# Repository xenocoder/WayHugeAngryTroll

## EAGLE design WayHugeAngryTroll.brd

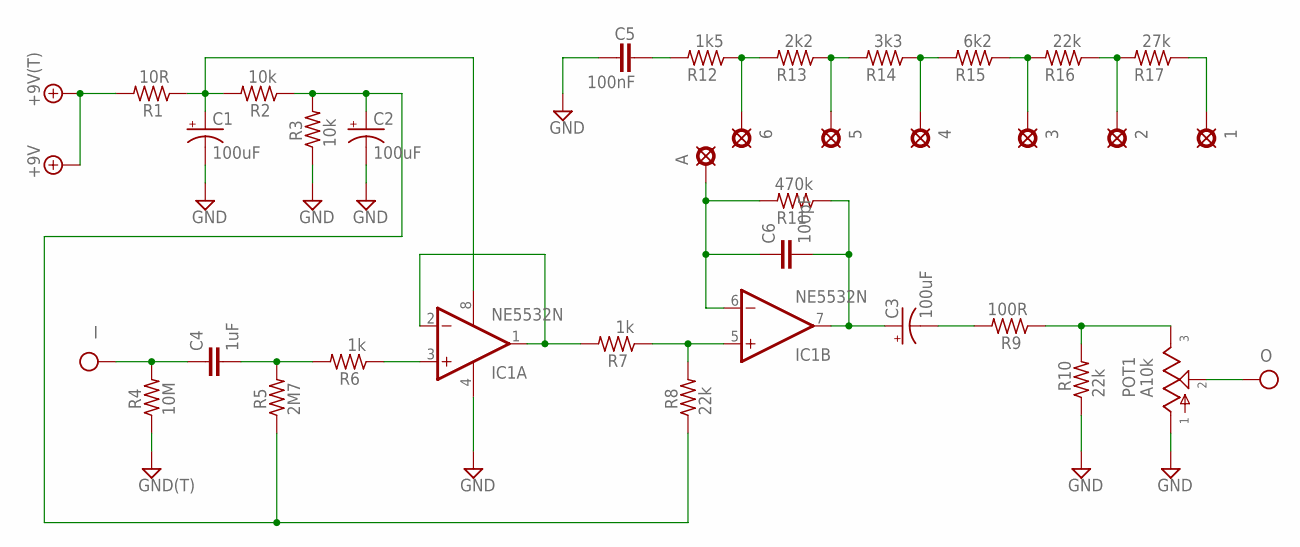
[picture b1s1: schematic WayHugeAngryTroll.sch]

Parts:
1, 2, 3, 4, 5, 6: PAD8; OCTOGON
+9: +9V(T); SQUARE
A: PAD8; OCTOGON
C1, C2, C3: 100uF; 063_025
C4: 1uF; 080X050
C5: 100nF; 072X035
C6: 100pF; 050X030_025
G: GND(T); SQUARE
I: IN(T); SQUARE
IC1: NE5532N; DIL08
O: OUT(T); SQUARE
POT1: A10k; 16MM-ROUND
R1: 10R; R0207/3
R2, R3: 10k; R0207/3
R4: 10M; R0207/3
R5: 2M7; R0207/3
R6, R7: 1k; R0207/3
R8, R10, R16: 22k; R0207/3
R9: 100R; R0207/3
R11: 470k; R0207/3
R12: 1k5; R0207/3
R13: 2k2; R0207/3
R14: 3k3; R0207/3
R15: 6k2; R0207/3
R17: 27k; R0207/3

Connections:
+9V: +9.1, R1.2
GND: C1.-, C2.-, C5.1, G.1, IC1.4 (V-), POT1.1, R3.1, R4.1, R10.1
IN: C4.1, I.1, R4.2
unnamed: C1.+, IC1.8 (V+), R1.1, R2.2
unnamed: C2.+, R2.1, R3.2, R5.1, R8.1
unnamed: C4.2, R5.2, R6.2
unnamed: IC1.3 (+IN), R6.1
unnamed: IC1.1 (OUT), IC1.2 (-IN), R7.2
unnamed: C5.2, R12.2
unnamed: IC1.5 (+IN), R7.1, R8.2
unnamed: 6.1, R12.1, R13.2
unnamed: POT1.3, R9.1, R10.2
unnamed: 5.1, R13.1, R14.2
unnamed: C3.+, C6.2, IC1.7 (OUT), R11.1
unnamed: C3.-, R9.2
unnamed: A.1, C6.1, IC1.6 (-IN), R11.2
unnamed: 4.1, R14.1, R15.2
unnamed: 3.1, R15.1, R16.2
unnamed: 2.1, R16.1, R17.2
unnamed: 1.1, R17.1
OUT: O.1, POT1.2

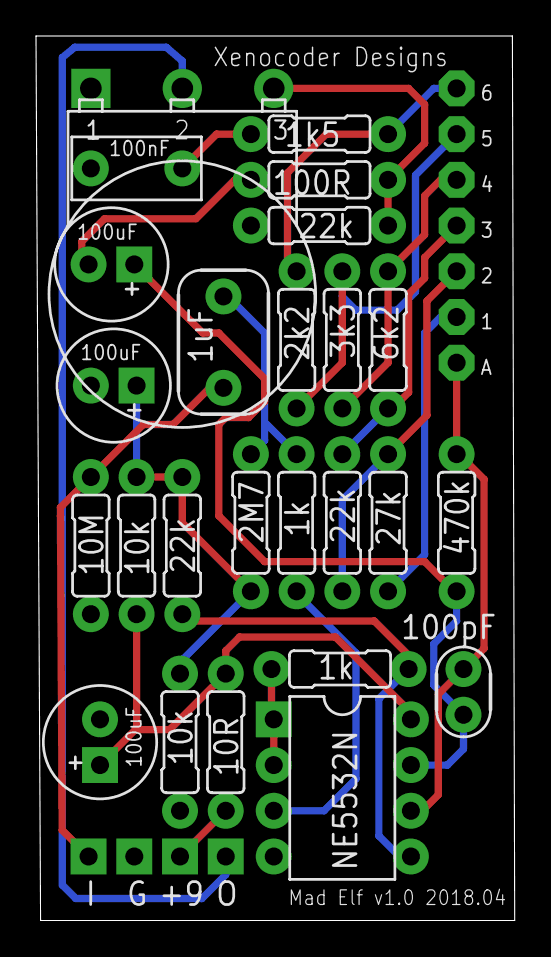
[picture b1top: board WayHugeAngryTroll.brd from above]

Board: 2 copper layers, 26.6 x 49.1 mm, 36 parts (0 on the bottom side), 21 nets.

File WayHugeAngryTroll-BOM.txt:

Partlist

Exported from WayHugeAngryTroll.sch at 9/5/18 7:34 PM

EAGLE Version 9.1.0 Copyright (c) 1988-2018 Autodesk, Inc.

Assembly variant: 

Part     Value          Device       Package     Library          Sheet

+9       +9V(T)         +9V(T)       SQUARE      mb_supply        1
1                       PAD8         OCTOGON     mb_supply        1
2                       PAD8         OCTOGON     mb_supply        1
3                       PAD8         OCTOGON     mb_supply        1
4                       PAD8         OCTOGON     mb_supply        1
5                       PAD8         OCTOGON     mb_supply        1
6                       PAD8         OCTOGON     mb_supply        1
A                       PAD8         OCTOGON     mb_supply        1
C1       100uF          0631         063_025     mb_caps-electro  1
C2       100uF          0631         063_025     mb_caps-electro  1
C3       100uF          0631         063_025     mb_caps-electro  1
C4       1uF            080X0502     080X050     mb_caps-chicklet 1
C5       100nF          072X0352     072X035     mb_caps-box      1
C6       100pF          050X030_0251 050X030_025 mb_caps-ceramic  1
G        GND(T)         GND(T)       SQUARE      mb_supply        1
I        IN(T)          IN(T)        SQUARE      mb_supply        1
IC1      NE5532N        NE5532N      DIL08       mb_ics           1
O        OUT(T)         OUT(T)       SQUARE      mb_supply        1
POT1     A10k           POTR         16MM-ROUND  mb_pots          1
R1       10R            6MM.3        R0207/3     mb_resistors     1
R2       10k            6MM.3        R0207/3     mb_resistors     1
R3       10k            6MM.3        R0207/3     mb_resistors     1
R4       10M            6MM.3        R0207/3     mb_resistors     1
R5       2M7            6MM.3        R0207/3     mb_resistors     1
R6       1k             6MM.3        R0207/3     mb_resistors     1
R7       1k             6MM.3        R0207/3     mb_resistors     1
R8       22k            6MM.3        R0207/3     mb_resistors     1
R9       100R           6MM.3        R0207/3     mb_resistors     1
R10      22k            6MM.3        R0207/3     mb_resistors     1
R11      470k           6MM.3        R0207/3     mb_resistors     1
R12      1k5            6MM.3        R0207/3     mb_resistors     1
R13      2k2            6MM.3        R0207/3     mb_resistors     1
R14      3k3            6MM.3        R0207/3     mb_resistors     1
R15      6k2            6MM.3        R0207/3     mb_resistors     1
R16      22k            6MM.3        R0207/3     mb_resistors     1
R17      27k            6MM.3        R0207/3     mb_resistors     1

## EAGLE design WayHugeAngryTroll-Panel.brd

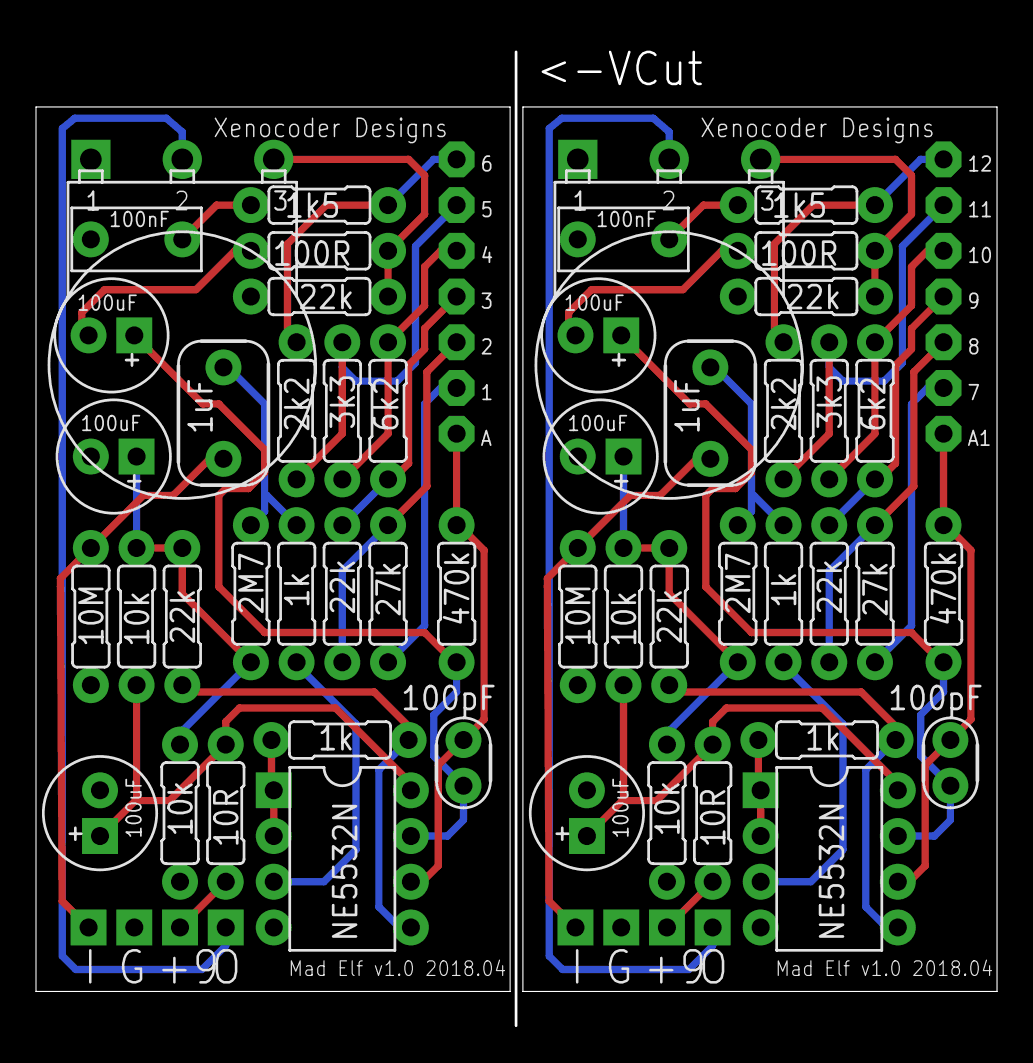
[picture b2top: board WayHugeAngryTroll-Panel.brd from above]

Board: 2 copper layers, 53.2 x 54.9 mm, 72 parts (0 on the bottom side), 42 nets.

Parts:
1, 2, 3, 4, 5, 6, 7, 8, 9, 10, 11, 12: OCTOGON
+1, +9: +9V(T); SQUARE
A, A1: OCTOGON
C1, C2, C3, C7, C8, C9: 100uF; 063_025
C4, C10: 1uF; 080X050
C5, C11: 100nF; 072X035
C6, C12: 100pF; 050X030_025
G, G1: GND(T); SQUARE
I, I1: IN(T); SQUARE
IC1, IC2: NE5532N; DIL08
O, O1: OUT(T); SQUARE
POT1, POT2: A10k; 16MM-ROUND
R1, R18: 10R; R0207/3
R2, R3, R27, R28: 10k; R0207/3
R4, R29: 10M; R0207/3
R5, R30: 2M7; R0207/3
R6, R7, R31, R32: 1k; R0207/3
R8, R10, R16, R19, R25, R33: 22k; R0207/3
R9, R34: 100R; R0207/3
R11, R20: 470k; R0207/3
R12, R21: 1k5; R0207/3
R13, R22: 2k2; R0207/3
R14, R23: 3k3; R0207/3
R15, R24: 6k2; R0207/3
R17, R26: 27k; R0207/3

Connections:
+9V: +9.1, R1.2
+9V1: +1.1, R18.2
GND: C1.-, C2.-, C5.1, G.1, IC1.4, POT1.1, R3.1, R4.1, R10.1
GND1: C7.-, C8.-, C11.1, G1.1, IC2.4, POT2.1, R19.1, R28.1, R29.1
IN: C4.1, I.1, R4.2
IN1: C10.1, I1.1, R29.2
unnamed: C1.+, IC1.8, R1.1, R2.2
unnamed: C2.+, R2.1, R3.2, R5.1, R8.1
unnamed: C4.2, R5.2, R6.2
unnamed: IC1.3, R6.1
unnamed: IC1.1, IC1.2, R7.2
unnamed: C5.2, R12.2
unnamed: IC1.5, R7.1, R8.2
unnamed: 6.1, R12.1, R13.2
unnamed: POT1.3, R9.1, R10.2
unnamed: 5.1, R13.1, R14.2
unnamed: C3.+, C6.2, IC1.7, R11.1
unnamed: C3.-, R9.2
unnamed: A.1, C6.1, IC1.6, R11.2
unnamed: 4.1, R14.1, R15.2
unnamed: 3.1, R15.1, R16.2
unnamed: 2.1, R16.1, R17.2
unnamed: 1.1, R17.1
unnamed: C7.+, IC2.8, R18.1, R27.2
unnamed: C8.+, R27.1, R28.2, R30.1, R33.1
unnamed: C10.2, R30.2, R31.2
unnamed: IC2.3, R31.1
unnamed: IC2.1, IC2.2, R32.2
unnamed: IC2.5, R32.1, R33.2
unnamed: POT2.3, R19.2, R34.1
unnamed: C9.+, C12.2, IC2.7, R20.1
unnamed: C9.-, R34.2
unnamed: A1.1, C12.1, IC2.6, R20.2
unnamed: C11.2, R21.2
unnamed: 12.1, R21.1, R22.2
unnamed: 11.1, R22.1, R23.2
unnamed: 10.1, R23.1, R24.2
unnamed: 9.1, R24.1, R25.2
unnamed: 8.1, R25.1, R26.2
unnamed: 7.1, R26.1
OUT: O.1, POT1.2
OUT1: O1.1, POT2.2

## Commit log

2018-08-24 First commit for Seeed Studios
2018-09-06 Added partslist
2018-10-19 Drill Guide
